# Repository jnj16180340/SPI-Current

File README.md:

# SPI-Current
Schematic and boards for power supply  

**Versions: **
Beefy and Wimpy: Wimpy has heatsinks+coils removed; traces are smaller; board is shrunk a lot

**TODO:**  
* Wall voltage fuse, stepdown, rectify, filter
* Make a branch with 2 independent half bridges in it
* Isolate the 12V stuff from the 5v stuff
* Figure out filtering caps for hall sensors
* Add fuse to output
* Lay out boards  

**NOTES:** 
* Traces won't take much current-- Only about 5 amps or so. Ideally we can OMIT the traces entirely and wire up with wire. Or, beel up the traces with solder by OMITTING the mask
* Use 10 gauge wire
* Replace shunt resistors x2 with thick wire jumper, unless you omit the hall sensors
* Replace a hall sensor with wire jumper unless you want two redundant ones
* Values for L#, may depend on the load
* Gain of output buffer: If ACS758 is 60mV/A, then max (50A) is 3. Want gain = 5/3
* 12V gets an XT60 connector, rated to 60A
* So does output to peltiers
* DIS jumper disables the drivers...
* If you power up the HIP4081 backwards it DIES.

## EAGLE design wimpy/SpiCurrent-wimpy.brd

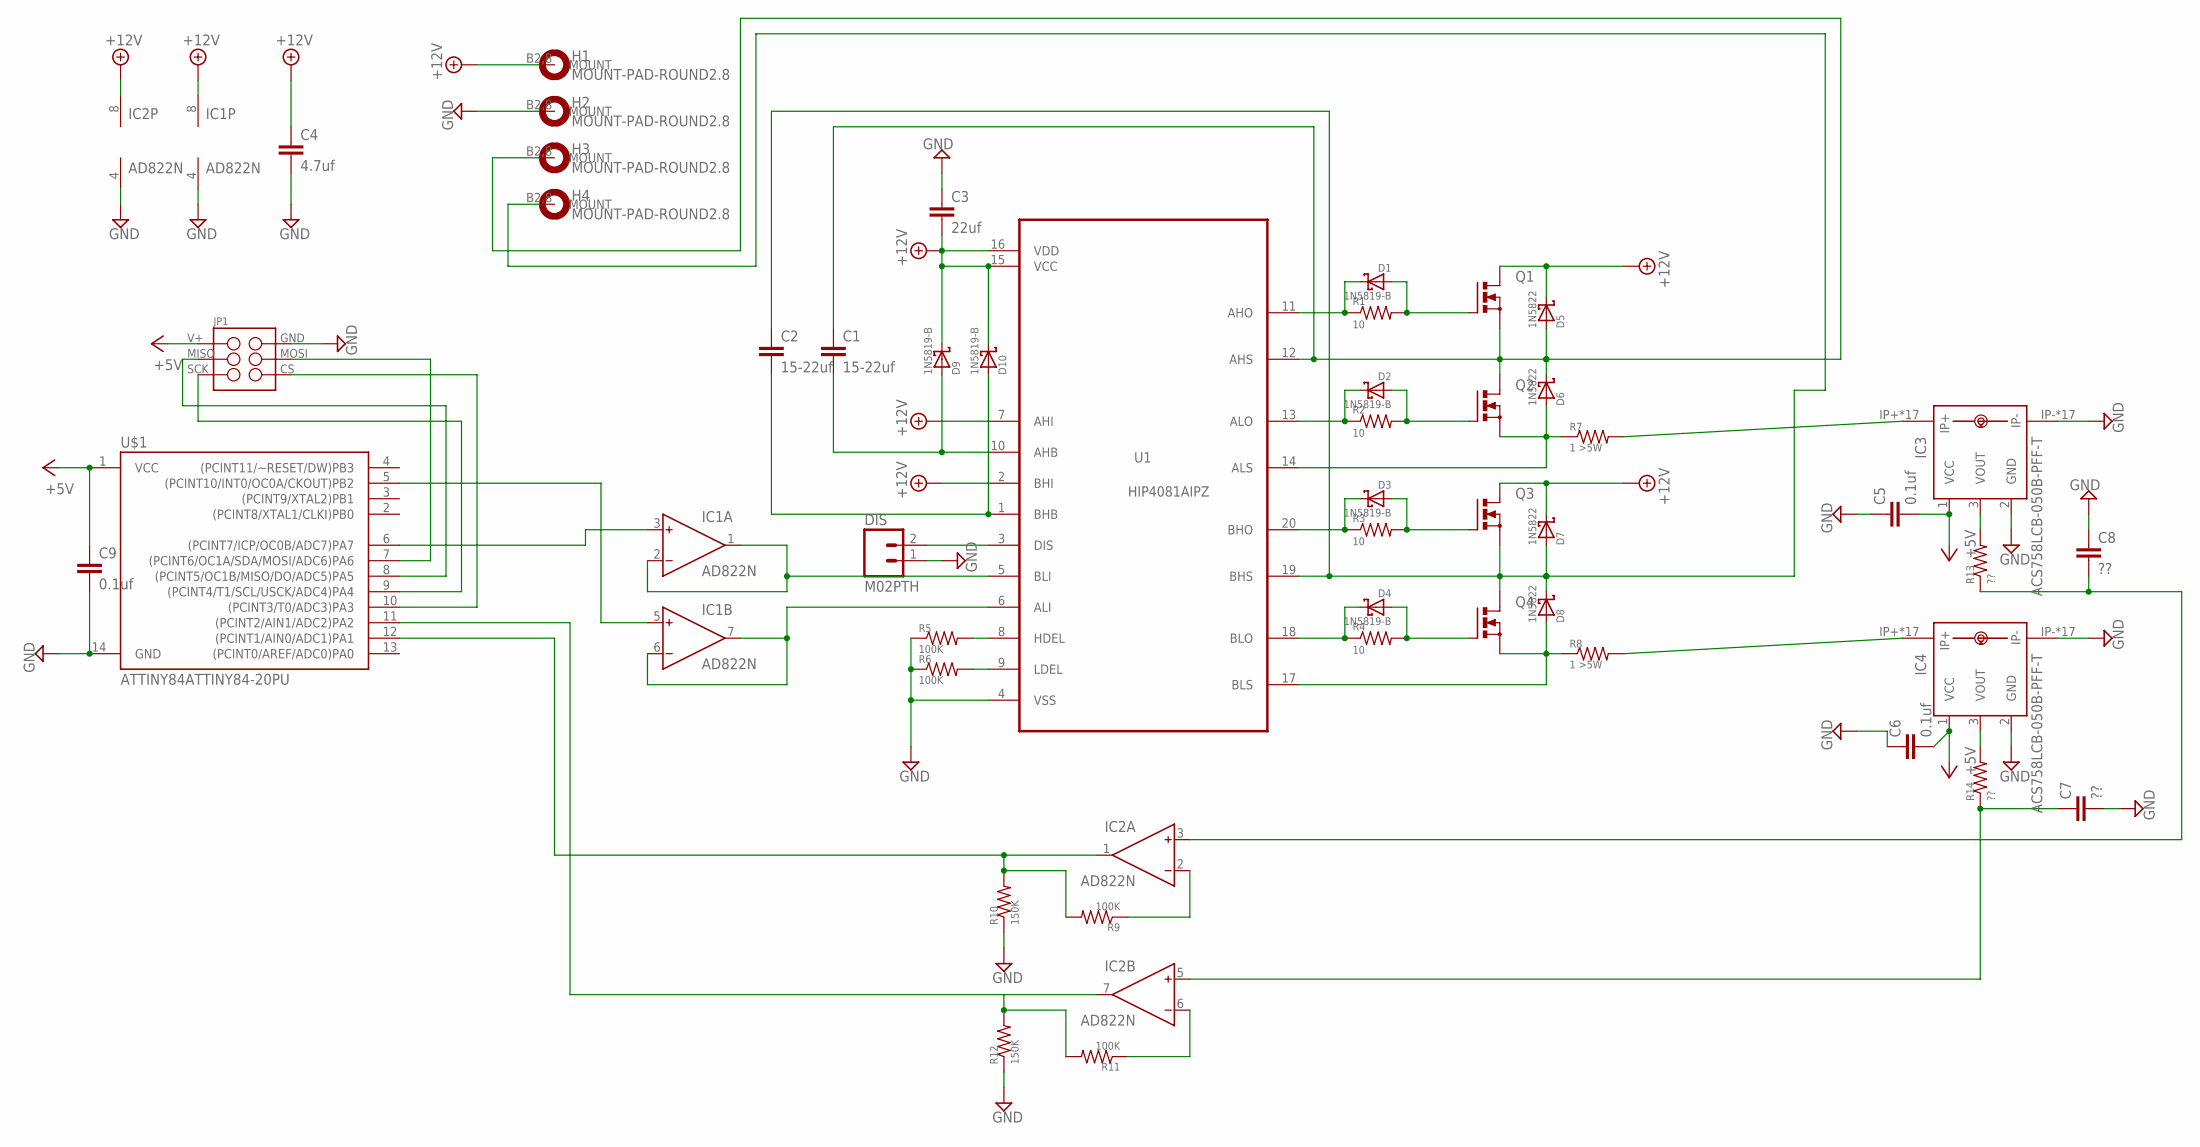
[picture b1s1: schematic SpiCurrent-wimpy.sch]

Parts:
C1, C2: 15-22uf; C050-055X075
C3: 22uf; C050-055X075
C4: 4.7uf; C050-055X075
C5, C6, C9: 0.1uf; C050-055X075
C7, C8: ??; C050-055X075
D1, D2, D3, D4, D9, D10: 1N5819-B; DO41-7.6
D5, D6, D7, D8: 1N5822; DO41-7.6
DIS: M02PTH; 1X02
H1, H2, H3, H4: MOUNT-PAD-ROUND2.8; 2,8-PAD
IC1, IC2: AD822N; DIL08
IC3, IC4: ACS758LCB-050B-PFF-T; CB-PFF
JP1: M03X2SHROUD; 2X3-SPI-SHROUDED
Q1, Q2, Q3, Q4: PMOSFET_NTO220BV; TO220BV
R1, R2, R3, R4: 10; 0207/10
R5, R6, R9, R11: 100K; 0207/10
R7, R8: 1 >5W; VTA54
R10, R12: 150K; 0207/10
R13, R14: ??; 0207/10
U1: HIP4081AIPZ; DIP254P762X533-20
U$1: ATTINY84ATTINY84-20PU; DIL14

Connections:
+5V: C5.2, C6.2, C9.1, IC3.1 (VCC), IC4.1 (VCC), JP1.1, U$1.1 (VCC)
+12V: C3.2, C4.1, D5.C, D7.C, D9.C, D10.C, H1.B2,8, IC1.8 (V+), IC2.8 (V+), Q1.D, Q3.D, U1.2 (BHI), U1.7 (AHI), U1.15 (VCC), U1.16 (VDD)
,JHBKLJN: C1.1, D5.A, D6.C, H3.B2,8, Q1.S, Q2.D, U1.12 (AHS)
GND: C3.1, C4.2, C5.1, C6.1, C7.2, C8.1, C9.2, DIS.1, H2.B2,8, IC1.4 (V-), IC2.4 (V-), IC3.2 (GND), IC3.IP-, IC3.IP-@2 (IP-), IC3.IP-@3 (IP-), IC3.IP-@4 (IP-), IC3.IP-@5 (IP-), IC3.IP-@6 (IP-), IC3.IP-@7 (IP-), IC3.IP-@8 (IP-), IC3.IP-@9 (IP-), IC3.IP-@10 (IP-), IC3.IP-@11 (IP-), IC3.IP-@12 (IP-), IC3.IP-@13 (IP-), IC3.IP-@14 (IP-), IC3.IP-@15 (IP-), IC3.IP-@16 (IP-), IC3.IP-@17 (IP-), IC4.2 (GND), IC4.IP-, IC4.IP-@2 (IP-), IC4.IP-@3 (IP-), IC4.IP-@4 (IP-), IC4.IP-@5 (IP-), IC4.IP-@6 (IP-), IC4.IP-@7 (IP-), IC4.IP-@8 (IP-), IC4.IP-@9 (IP-), IC4.IP-@10 (IP-), IC4.IP-@11 (IP-), IC4.IP-@12 (IP-), IC4.IP-@13 (IP-), IC4.IP-@14 (IP-), IC4.IP-@15 (IP-), IC4.IP-@16 (IP-), IC4.IP-@17 (IP-), JP1.2, R5.1, R6.1, R10.1, R12.1, U1.4 (VSS), U$1.14 (GND)
unnamed: IC1.1 (OUT), IC1.2 (IN-), U1.5 (BLI)
unnamed: IC1.6 (IN-), IC1.7 (OUT), U1.6 (ALI)
unnamed: D3.C, R3.1, U1.20 (BHO)
unnamed: D3.A, Q3.G, R3.2
unnamed: D4.C, R4.1, U1.18 (BLO)
unnamed: D4.A, Q4.G, R4.2
unnamed: D2.C, R2.1, U1.13 (ALO)
unnamed: D2.A, Q2.G, R2.2
unnamed: D1.C, R1.1, U1.11 (AHO)
unnamed: D1.A, Q1.G, R1.2
unnamed: R5.2, U1.8 (HDEL)
unnamed: R6.2, U1.9 (LDEL)
unnamed: C2.1, D7.A, D8.C, H4.B2,8, Q3.S, Q4.D, U1.19 (BHS)
unnamed: D6.A, Q2.S, R7.1, U1.14 (ALS)
unnamed: D8.A, Q4.S, R8.1, U1.17 (BLS)
unnamed: C1.2, D9.A, U1.10 (AHB)
unnamed: C2.2, D10.A, U1.1 (BHB)
unnamed: DIS.2, U1.3 (DIS)
unnamed: JP1.4, U$1.7 ((PCINT6/OC1A/SDA/MOSI/ADC6)PA6)
unnamed: JP1.3, U$1.8 ((PCINT5/OC1B/MISO/DO/ADC5)PA5)
unnamed: JP1.5, U$1.9 ((PCINT4/T1/SCL/USCK/ADC4)PA4)
unnamed: JP1.6, U$1.10 ((PCINT3/T0/ADC3)PA3)
unnamed: IC1.5 (IN+), U$1.5 ((PCINT10/INT0/OC0A/CKOUT)PB2)
unnamed: IC1.3 (IN+), U$1.6 ((PCINT7/ICP/OC0B/ADC7)PA7)
unnamed: IC2.2 (IN-), R9.1
unnamed: IC4.IP+, IC4.IP+@2 (IP+), IC4.IP+@3 (IP+), IC4.IP+@4 (IP+), IC4.IP+@5 (IP+), IC4.IP+@6 (IP+), IC4.IP+@7 (IP+), IC4.IP+@8 (IP+), IC4.IP+@9 (IP+), IC4.IP+@10 (IP+), IC4.IP+@11 (IP+), IC4.IP+@12 (IP+), IC4.IP+@13 (IP+), IC4.IP+@14 (IP+), IC4.IP+@15 (IP+), IC4.IP+@16 (IP+), IC4.IP+@17 (IP+), R8.2
unnamed: IC2.1 (OUT), R9.2, R10.2, U$1.12 ((PCINT1/AIN0/ADC1)PA1)
unnamed: IC2.7 (OUT), R11.2, R12.2, U$1.11 ((PCINT2/AIN1/ADC2)PA2)
unnamed: IC2.6 (IN-), R11.1
unnamed: IC3.IP+, IC3.IP+@2 (IP+), IC3.IP+@3 (IP+), IC3.IP+@4 (IP+), IC3.IP+@5 (IP+), IC3.IP+@6 (IP+), IC3.IP+@7 (IP+), IC3.IP+@8 (IP+), IC3.IP+@9 (IP+), IC3.IP+@10 (IP+), IC3.IP+@11 (IP+), IC3.IP+@12 (IP+), IC3.IP+@13 (IP+), IC3.IP+@14 (IP+), IC3.IP+@15 (IP+), IC3.IP+@16 (IP+), IC3.IP+@17 (IP+), R7.2
unnamed: C8.2, IC2.3 (IN+), R13.1
unnamed: C7.1, IC2.5 (IN+), R14.1
unnamed: IC3.3 (VOUT), R13.2
unnamed: IC4.3 (VOUT), R14.2

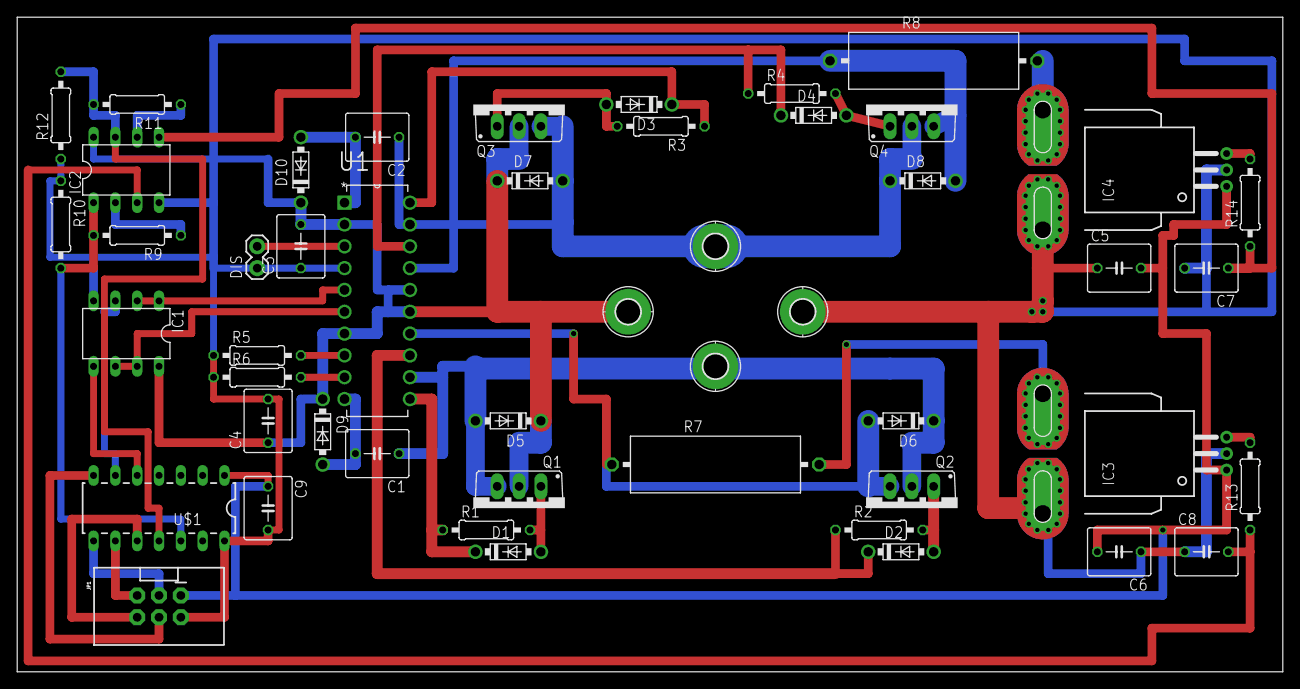
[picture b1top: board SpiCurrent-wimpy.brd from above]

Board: 2 copper layers, 147.3 x 76.2 mm, 49 parts (0 on the bottom side), 38 nets.

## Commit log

2015-01-28 blah
2015-02-02 added license
2015-02-02 ignore .directory
2015-02-13 Added MCU and hall effect sensor
2015-02-14 barely begun layout
2015-02-15 begun layout
2015-02-15 Grossly laid out; still need to check (C5 is weird), check traces, adjust trace widths etc
2015-02-16 Layout complete. NB fancy mask stuff is NOT complete, use this one for low(ish) current testing
2015-02-16 read me
2015-02-17 Made beefy abnd wimpy versions
2015-02-17 removed old crap

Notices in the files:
parts and their libraries:
SparkFun-Connectors: Licensing: Creative Commons ShareAlike 4.0 International - https://creativecommons.org/licenses/by-sa/4.0
